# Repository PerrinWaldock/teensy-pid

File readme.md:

# Teensy-based Intensity Feedback Controller Guide

This repository contains code and PCBs for creating Teensy microcontroller-based feedback controllers. They have been used to control the laser intensity on ultracold atom experiments because (a) they are relatively inexpensive and (b) they provide faster rise times than similarly-priced analog feedback controllers.

When used to lock to itself, the latest version of the PCB and firmwarecan achieve 
* a loop rate of 100 kHz
* a standard deviation of TODO
* a rise time of <10 us

## PCB-free Feedback Controller

The code in the `multistate` branch can be used without the PCB. It can only run a Teensy 3.2 because that microcontroller has 5V-tolerant digital inputs, and an inbuilt DAC. It uses two digital signals from digital outputs to select one of four setpoints which are configured over USB. It controls the voltage into a XM-B6H4-0404C-01.

However, this setup has some flaws:
* the inbuilt ADC and DAC are noisy, with only ~8-10 usable bits. This limits the feedback stability shown in the above posts.
* there is no input anti-aliasing filter
* the connections are soldered together on stripboard. The digital input controlling the LSB of the state is currently loose, so the feedback controller occasionally malfunctions when the digital input is not connected to the microcontroller
* the Teensy 3.2 is currently EOL so it is challenging to find a replacement.

A replacement PCB was built that provides the following features:
* input anti-aliasing filtering
* input and output buffering
* input over-voltage protection for both digital and analog inputs
* 16-bit ADCs and DACs
* a faster (600 MHz) microcontroller
* a separate +5V power supply for all analog electronics
* space on the board to mount an XM-B6H4-0404C-01.

The new PCB and its corresponding control code is in the `master` branch of the repository. Below is a guide to the PCB and control code:

## PCB Important Components
The KiCAD design files and schematics are in the schematics folder of this repository. Below is a guide to some components that can be populated or depopulated to change the performance characteristics of the board:
* R1: Populate this to give this board a 50-ohm terminated input. This can be useful when interfacing with a [PDA100A2](https://www.thorlabs.com/thorproduct.cfm?partnumber=PDA100A2) because they produce a 0-5V output when terminated with a 50 ohm load.
  * One can also modify the values of R1, R2 to remove a DC offset from the input signal, or modify the values of R7 and R9 to amplify the input. Useful if the input is a small signal.
* R3: Populate this to bypass the input op amp. Do not do this without first disconnecting the op amp from by depopulating R2 and R9. Often used when R15 and R17 are populated to use the Teensy internal ADC instead of the external ADC (not recommended).
* C1 and R7: Change these values to change the input op amp filter (currently not populated).
* R16 and R18. ONLY POPULATE ONE OF THESE AT A TIME. Used to select 5V or 3.3V reference. If 5V reference is selected (R18), make sure to depopulate R6 so that the input voltage range is the full 0V-5V.
* R34: Populate to use external 5V instead of USB 5V power. DO NOT DO THIS WITHOUT FIRST COVERING THE PIN THAT SUPPLIES POWER ON THE USB CABLE: https://community.octoprint.org/t/put-tape-on-the-5v-pin-why-and-how/13574
* R40: Populate to bypass the output buffer. Do not do this without first disconnecting the op amp by depopulating R41 and FB2.

## Software Important Preprocessor Directives
`pins.h` specifies the IO pins:
* `PIN_REFERENCE0` and `PIN_REFERENCE1` are used to select which preprogrammed set voltage the feedback controller will try to attain.
* `PIN_REFERENCE` can be used as a traditional analog setpoint (NOTE: The PCB is not currently set up to support this)

The `settings.h` file can be changed to modify the feedback controller's behaviour:
* `DEFAULT_KP`, `DEFAULT_KI`, and `DEFAULT_KD` are the default values for the PID constants. They may be overwritten on startup if `LOAD_ON_STARTUP` is enabled.
* `DEFAULT_LOOP_RATE` sets the default loop rate for the feedback controller. It may be overwritten on startup. If `PRECISE_LOOP_TIMING` is true, the feedback controller will run the feedback control loop at the loop rate; otherwise, the loop rate is ignored and the control loop will run as fast as possible. Disabling the precise timing increases the maximum frequency that can be compensated for but means that the units of the PID constants are incorrect.
* `OUTPUT_SETTLE_DELAY_US` should be set to the response time of the output stage (e.g. if controlling an AOM, the response time of the voltage variable attenuator). It is a delay that kicks in immediately after the set point changes from off to on.
  * When the output changes state from off (below the minimum set point) to on (between the minimum and maximum setpoint), the feedback calculation is skipped for the first output, and only the feedforward value is used. This allows the feedback controller to rapidly approach the desired value. However, it takes a finite amount of time for the system to reach the desired value. This delay stops the next feedback measurement from being taken before the system settles to its new state.
* `SERIAL_BAUD` sets the baud rate to communicate with the computer. Comment it out to disable USB communication
  * `SERIAL_CHECK_PERIOD_MS` sets the period to communicate with the host computer. `DEFAULT_PRINT_PERIOD_MS` sets the print period of the PID state.
* `INPUT_MODE` sets the type of input that the feedback controller uses to select its state. `DIGITAL_INPUT` selects preprogrammed set voltage number `PIN_REFERENCE1*2 + PIN_REFERENCE0`, `ANALOG_INPUT` uses the voltage on `PIN_REFERENCE`, and `SOFTWARE_INPUT` only accepts software changes to the set voltage. Note that the `ANALOG_INPUT` mode is not currently well-tested.
  * It may be advantageous to reduce `ANALOG_REFERENCE_RESOLUTION` to 8 or lower to speed up the loop frequency.
  * `NUM_SETPOINTS` is the number of setpoints that can be selected in digital mode. Do not change this without changing the PCB and number of setpoint pins.
* `FEEDFORWARD` enables feedforward control. One can characterize the transfer function of the system via a serial command, then perform corrections to the feedforward function using PID. It generally produces faster rise times than standard PID feedback control, but the `CALIBRATION_SETTLE_DELAY_US` value must be set carefully so that the feedforward array is generated accurately.
* `NEGATIVE_OUTPUT_SLOPE` should be set to true if a larger output voltage should produce a smaller input voltage and vice versa.
* `SAVE_DATA` will give the option to save PID constants, loop frequency, setpoint and output limits, setpoints, and feedforward data.
  * If `LOAD_ON_STARTUP`, then these constants will be loaded on startup, overriding the default values.
* `DEFAULT_SETPOINT` is the default setpoint voltage. This will be overridden if `LOAD_ON_STARTUP` is set to true.
* `DEFAULT_READ_AVERAGES_POWER` sets the default number of averages that will be taken before using a feedback measurement. The number of averages is two to the power of the value. This will be overridden if `LOAD_ON_STARTUP` is set to true.
  * If in analog mode, `ANALOG_READ_AVERAGES` is the number of averages for the setpoint value reading, and `ANALOG_REFERENCE_RESOLUTION` sets the number of bits for the measurement.
* if `RECORD_FEEDBACK_ALL_ITERATIONS` is true, then the feedback voltage will always be measured, even if it isn't used (such as immediately after a setpoint is changed). This can be helpful for debugging but should be turned off for performance.
* if `TIME_FEEDBACK_LOOP`, the length of time to perform the pid calculation will be timed.
* if `RECORD_INPUT`, input values will be logged to RAM. Helpful for debugging.
* `CALIBRATION_AVERAGES` sets the number of measurements to take of each point when generating the feedforward lookup array
  * `CALIBRATION_PRE_SETTLE_DELAY_US` sets how long to wait (in us) for the system to settle before measuring points for the feedforward lookup array
  * `CALIBRATION_SETTLE_DELAY_US` sets how how long to wait (in us) for the system to settle between points while measuring points for the feedforward lookup array

## Serial Commands
Connect the feedback controller using Putty or the Arduino IDE to tune the feedback parameters, adjust the setpoint, loop frequency, and other parameters.

Note that the FeedbackController class in the Prometheus repository uses some of the following serial commands in order to set the laser power to a certain level at specific points in a recipe.

Commands:
* `h` to print the help menu
* `kp=x` to set the proportional constant. `kp?` to print the proportional constant. Similar for `ki` and `kd`.
* `sv0=0.5` to set the 0th preprogammed set voltage to 0.5 volts. similar for `sv1`, `sv2`, and `sv3`. use `sv?` to view all for set voltages. Use `sp` to set the value as an integer instead of as a voltage.
* `ls=0.05` to set the minimum setpoint to 0.05V. Set to some value close to the minimum attainable feedback value. Used to prevent integral wind-up if the system cannot reach the set value.
* `ls=4.5` to set the maximum setpoint to 4.5V. Set to some value close to the maximum attainable feedback value. Used to prevent integral wind-up if the system cannot reach the set value.
* `lf=2000` to set the loop frequency to 2000 Hz. lf? to view the loop frequency. Make sure that the loop period is not less than the time the controller takes to perform a pid calculation.
* `ra=2` to set the number of read averages to four. The formula is <read averages>=2^x where x is an integer -- this ensures that the number of read averages is always a multiple of two, which speeds up the averaging process. Use ra? to view the number of read averages
* `pa=1` to enable feedback control, `pa=0` to disable it
* `po=1` to print sample feedback control values. `po=0` to disable the printed sample feedback control values. A sample string would be `s:6553	 f:6553	 ff:13490	 o:12850	 t:16`, where s refers to the set voltage, f is the feedback voltage, ff is the output voltage the feedforward term recommends, o is the output voltage of the controller, and t is the time the controller took to perform the feedback calculation. All voltages are written as integers, and the time is in microseconds. Write `po=2` to display the values as voltages instead.
* `cf` to create the feedforward function. This will also set the setpoint limits to slightly inside the feedback controller range. Write `cd?` to print out the calibration data, and `ce?` to print out the calibration extrema (minimum and maximum set voltage).
* `ew=w` to write the feedback constants, loop rate, and calibration data to EEPROM so they are persistent after startup. `ew=r` to read all data from EEPROM. Useful when tuning to restore the feedback controller to a working state.
* `cl` to clear the integral term and reset the controller state -- helpful if the integral term has spooled up.

Typical usage:
Via the USB serial connection, enter the following comnmands:
* `cf=1` (to calibrate the feedforward function)
* `ce?` (to print the minimum and maximum values that can theoretically be set)
* `sv0=1` (to set the set voltage to 1V. Replace the 1 with a value close to the maximum set voltage found above)
* `po=2` (monitor the output, ensure that it is stable)
* `po=0` (turn off the output)
* set the tuning parameters and loop frequency with `ki=x`,`kp=x`,`kd=0`, `lf=100000`. Ensure that the calculation time does not exceed the loop period. Adjust parameters until performance is satisfactory.

### Notes for the UBC QDG Lab
To achieve a rapid response time, the set point needs to be selected using the digital inputs. It is easiest to do so by programming the desired setpoints ahead of time, then selecting the desired set point via the digital input. Code to do this is in the FeedbackController class in hardware/FeedbackController in the [Prometheus repository](https://qdg-code.phas.ubc.ca:2633/Perrin/PrometheusPython). This class automatically uses USB commands to assign different set voltages to different set voltage states during the recipe's compile time, then uses digital outputs to select those states while the recipe is executing. It automatically calibrates the feedforward function during compile time.

## Programming Instructions
This was developed as a PlatformIO project in VS Code. The easiest way to modify and compile it is to get the PlatformIO VS Code extension

## GUI and Python Scripts

## Future Work To Do
### Speeding things up
Currently, the microcontroller is set to use a 600 MHz clock. Attaching a heatsink to the processor should allow high clock rates.

Higher clock rates may disrupt communication with the ADC and DAC. To improve the ADC and DAC throughput:
* connect an oscilloscope to the data lines as well as the analog output
* change "#define dacdigwr(p, s) digitalWrite(p, s)" in dac.ino to "#define dacdigwr(p, s) digitalWriteFast(p, s)"
* adjust WRITE_DELAY_NS such that the DAC still consistantly writes the correct value
* similarly, adjust WAIT_TIME_NS and CLOCK_DELAY_NS in adc.ino.
* R21, R22, R23, R24, R25, R26, R30, R31, and R32 may need to be adjusted to a smaller value to accommodate higher clock rates. Choose values that are as large as possible while still allowing the clock to remain high for the specified time in the ADC and DAC datasheets.

### Testing
* The latest version of the PCB (V3.0) has not been tested as a feedback controller for a laser intensity lock.
* Using the analog input as a setpoint also is not well-tested, and may contain bugs.

### New Algorithms
This controller should be usable for a gradient-descent saturated adsorption lock algorithm.

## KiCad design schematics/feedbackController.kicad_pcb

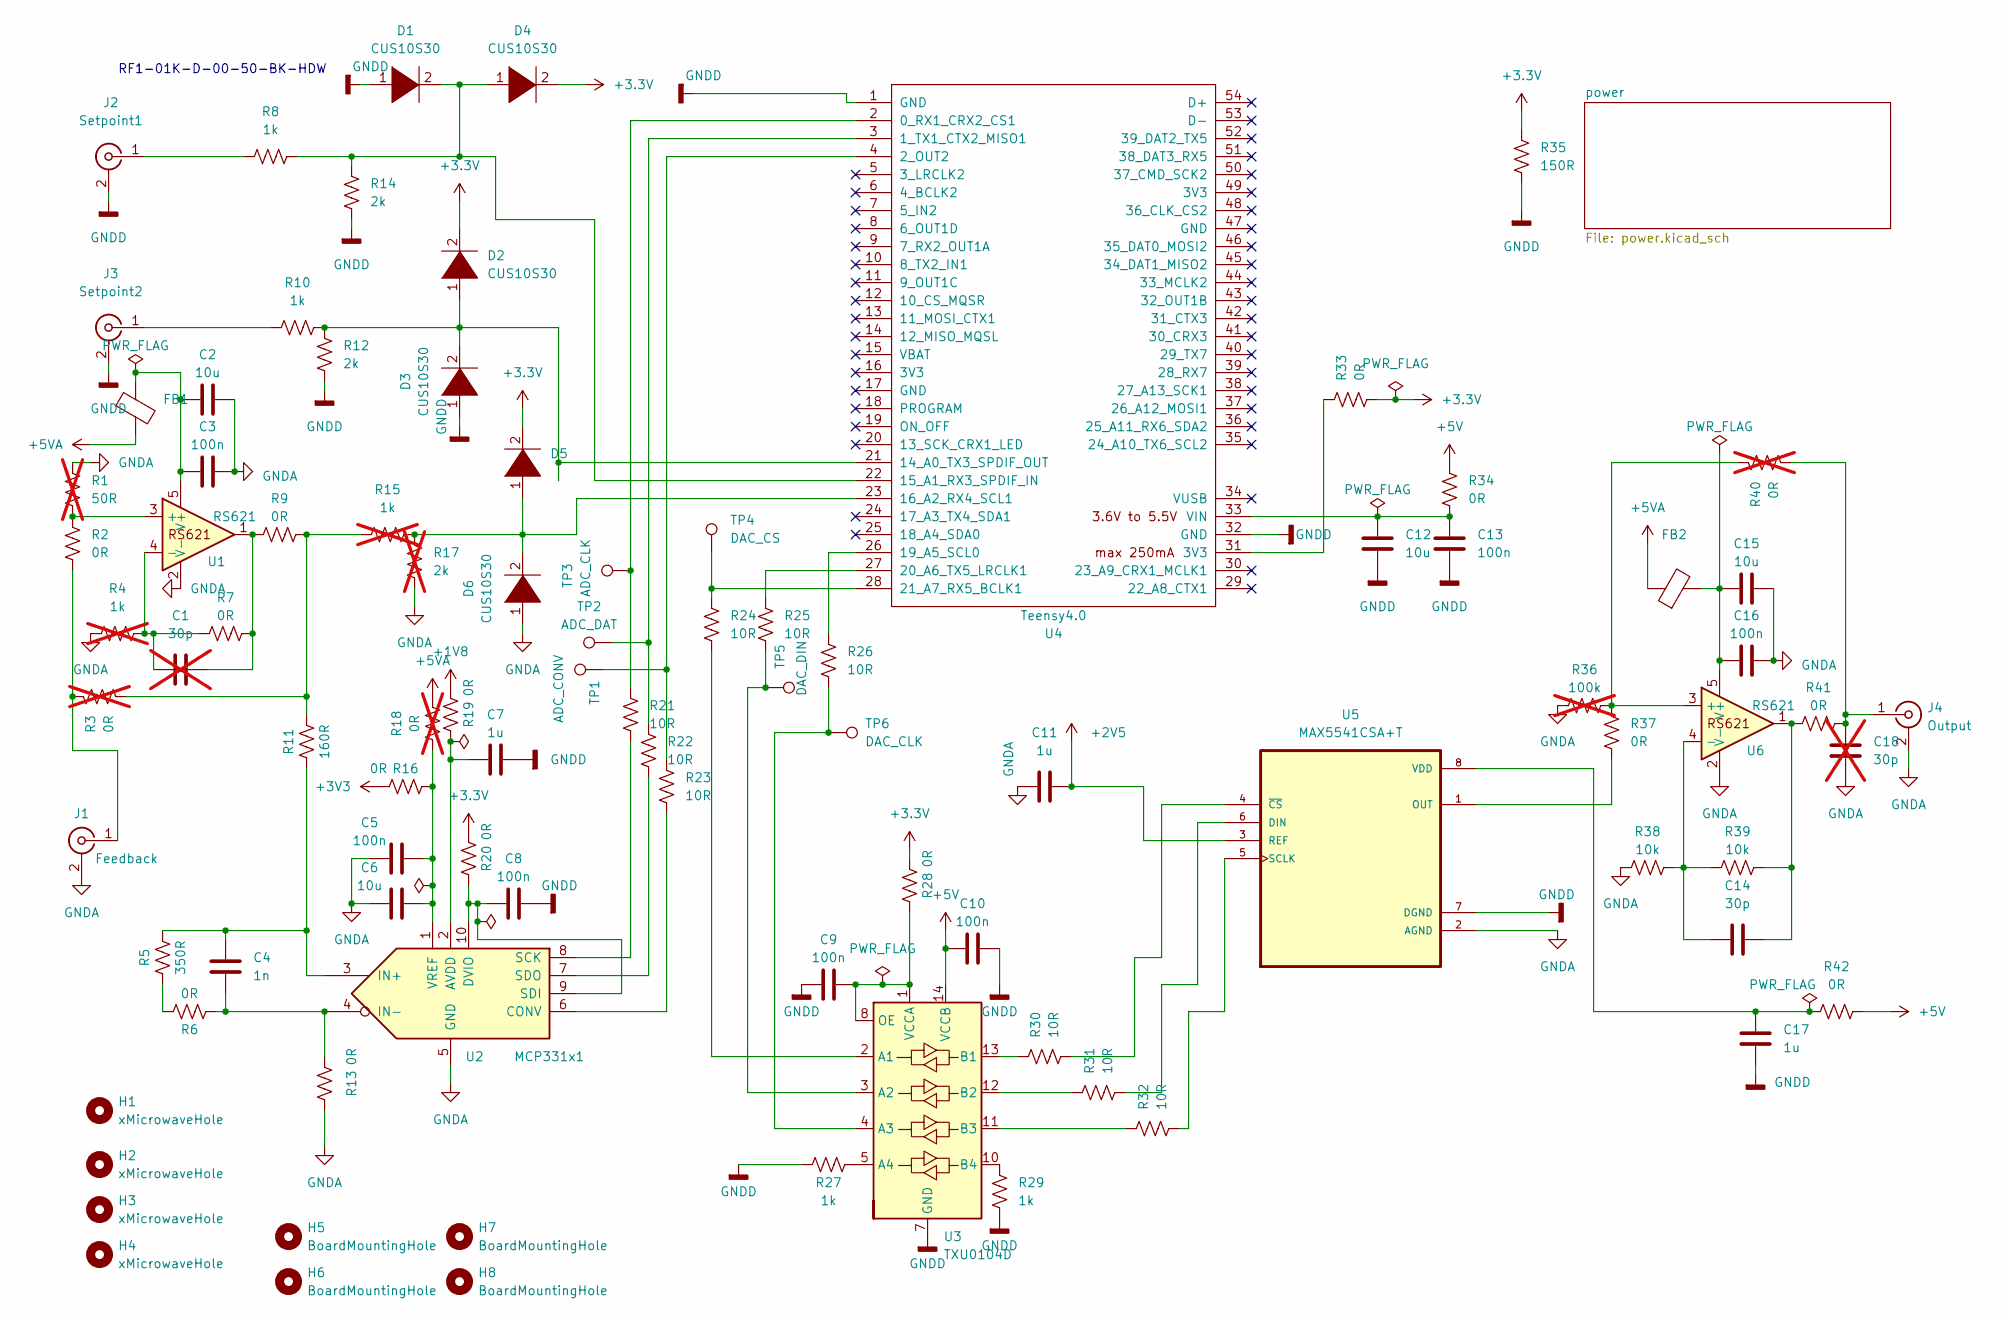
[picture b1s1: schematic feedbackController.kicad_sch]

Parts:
C1, C18: 30p; C_0805_2012Metric; not fitted
C2, C6, C12, C15: 10u; C_0805_2012Metric
C3, C5, C8, C9, C10, C13, C16: 100n; C_0805_2012Metric
C4: 1n; C_0805_2012Metric
C7, C11, C17: 1u; C_0805_2012Metric
C14: 30p; C_0805_2012Metric
D1, D2, D3, D4, D5, D6: CUS10S30; D_SOD-323_HandSoldering
FB1, FB2: FerriteBead; R_0805_2012Metric_Pad1.20x1.40mm_HandSolder
H1, H2, H3, H4: xMicrowaveHole; MountingHole_2.1mm
H5, H6, H7, H8: BoardMountingHole; MountingHole_3.2mm_M3
J1: Feedback; BNC_Amphenol_B6252HB-NPP3G-50_Horizontal
J2: Setpoint1; BNC_Amphenol_B6252HB-NPP3G-50_Horizontal
J3: Setpoint2; BNC_Amphenol_B6252HB-NPP3G-50_Horizontal
J4: Output; BNC_Amphenol_B6252HB-NPP3G-50_Horizontal
R1: 50R; R_0805_2012Metric; not fitted
R2, R6, R7, R9, R13, R16, R19, R20, R28, R33, R34, R37, R41, R42: 0R; R_0805_2012Metric
R3, R18, R40: 0R; R_0805_2012Metric; not fitted
R4, R15: 1k; R_0805_2012Metric; not fitted
R5: 350R; R_0805_2012Metric
R8, R10, R27, R29: 1k; R_0805_2012Metric
R11: 160R; R_0805_2012Metric
R12, R14: 2k; R_0805_2012Metric
R17: 2k; R_0805_2012Metric; not fitted
R21, R22, R23, R24, R25, R26, R30, R31, R32: 10R; R_0805_2012Metric
R35: 150R; R_0805_2012Metric
R36: 100k; R_0805_2012Metric; not fitted
R38, R39: 10k; R_0805_2012Metric
TP1: ADC_CONV; TestPoint_Loop_D2.50mm_Drill1.0mm
TP2: ADC_DAT; TestPoint_Loop_D2.50mm_Drill1.0mm
TP3: ADC_CLK; TestPoint_Loop_D2.50mm_Drill1.0mm
TP4: DAC_CS; TestPoint_Loop_D2.50mm_Drill1.0mm
TP5: DAC_DIN; TestPoint_Loop_D2.50mm_Drill1.0mm
TP6: DAC_CLK; TestPoint_Loop_D2.50mm_Drill1.0mm
U1, U6: RS621; SOT-23-5_HandSoldering
U2: MCP331x1; MSOP-10_3x3mm_P0.5mm
U3: TXU0104D; SOIC-14_3.9x8.7mm_P1.27mm
U4: Teensy4.0; Teensy40
U5: MAX5541CSA+T; SOIC-8_3.9x4.9mm_P1.27mm

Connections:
+1V8: R19.2; also elsewhere on the board
+2V5: C11.2, U5.3 (REF); also elsewhere on the board
+3.3V: D2.2 (A), D4.2 (A), D5.2 (A), R20.2, R28.2, R33.1, R35.1; also elsewhere on the board
+3V3: R16.2; also elsewhere on the board
+5V: C10.1, R34.2, R42.2, U3.14 (VCCB); also elsewhere on the board
+5VA: FB1.2, FB2.1, R18.2; also elsewhere on the board
GNDA: C2.2, C3.2, C5.1, C6.1, C11.1, C15.2, C16.2, C18.2, D6.1 (K), J1.2 (Ext), J4.2 (Ext), R1.1, R4.1, R13.1, R17.2, R36.1, R38.1, U1.2 (V-), U2.5 (GND), U5.2 (AGND), U6.2 (V-); also elsewhere on the board
GNDD: C7.2, C8.2, C9.1, C10.2, C12.2, C13.2, C17.2, D1.1 (K), D3.1 (K), J2.2 (Ext), J3.2 (Ext), R12.2, R14.2, R27.1, R29.2, R35.2, U3.7 (GND), U4.1 (GND), U4.32 (GND), U5.7 (DGND); also elsewhere on the board
unnamed: C1.2, R7.2, R9.1, U1.1
unnamed: C14.2, R39.2, R41.1, U6.1
unnamed: D1.2 (A), D4.1 (K), R8.2, R14.1, U4.22 (15_A1_RX3_SPDIF_IN)
unnamed: D2.1 (K), D3.2 (A), R10.2, R12.1, U4.21 (14_A0_TX3_SPDIF_OUT)
unnamed: D5.1 (K), D6.2 (A), R15.2, R17.1, U4.23 (16_A2_RX4_SCL1)
unnamed: J1.1 (In), R2.2, R3.1
unnamed: J2.1 (In), R8.1
unnamed: J3.1 (In), R10.1
unnamed: C18.1, J4.1 (In), R40.2, R41.2
unnamed: R5.1, R6.2
unnamed: R3.2, R9.2, R11.2, R15.1
unnamed: R33.2, U4.31 (3V3)
unnamed: R1.2, R2.1, U1.3 (+)
unnamed: C1.1, R4.2, R7.1, U1.4 (-)
unnamed: C2.1, C3.1, FB1.1, U1.5 (V+)
unnamed: C7.1, R19.1, U2.2 (AVDD)
unnamed: R23.1, U2.6 (CONV)
unnamed: C8.1, R20.1, U2.9 (SDI), U2.10 (DVIO)
unnamed: C4.1, R5.2, R11.1, U2.3 (IN+)
unnamed: C4.2, R6.1, R13.2, U2.4 (IN-)
unnamed: R21.1, U2.8 (SCK)
unnamed: R22.1, U2.7 (SDO)
unnamed: C5.2, C6.2, R16.1, R18.1, U2.1 (VREF)
unnamed: R24.1, U3.2 (A1)
unnamed: R25.1, TP5.1, U3.3 (A2)
unnamed: R26.1, TP6.1, U3.4 (A3)
unnamed: R27.2, U3.5 (A4)
unnamed: R30.2, U3.13 (B1)
unnamed: R31.2, U3.12 (B2)
unnamed: R32.2, U3.11 (B3)
unnamed: R29.1, U3.10 (B4)
unnamed: C9.2, R28.1, U3.1 (VCCA), U3.8 (OE)
unnamed: R21.2, TP3.1, U4.2 (0_RX1_CRX2_CS1)
unnamed: R22.2, TP2.1, U4.3 (1_TX1_CTX2_MISO1)
unnamed: R23.2, TP1.1, U4.4 (2_OUT2)
unnamed: R26.2, U4.26 (19_A5_SCL0)
unnamed: R25.2, U4.27 (20_A6_TX5_LRCLK1)
unnamed: R24.2, TP4.1, U4.28 (21_A7_RX5_BCLK1)
unnamed: C12.1, C13.1, R34.1, U4.33 (VIN)
unnamed: R31.1, U5.6 (DIN)
unnamed: R37.1, U5.1 (OUT)
unnamed: R32.1, U5.5 (SCLK)
unnamed: C17.1, R42.1, U5.8 (VDD)
unnamed: R30.1, U5.4 (~CS)
unnamed: R36.2, R37.2, R40.1, U6.3 (+)
unnamed: C14.1, R38.2, R39.1, U6.4 (-)
unnamed: C15.1, C16.1, FB2.2, U6.5 (V+)

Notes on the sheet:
RF1-01K-D-00-50-BK-HDW

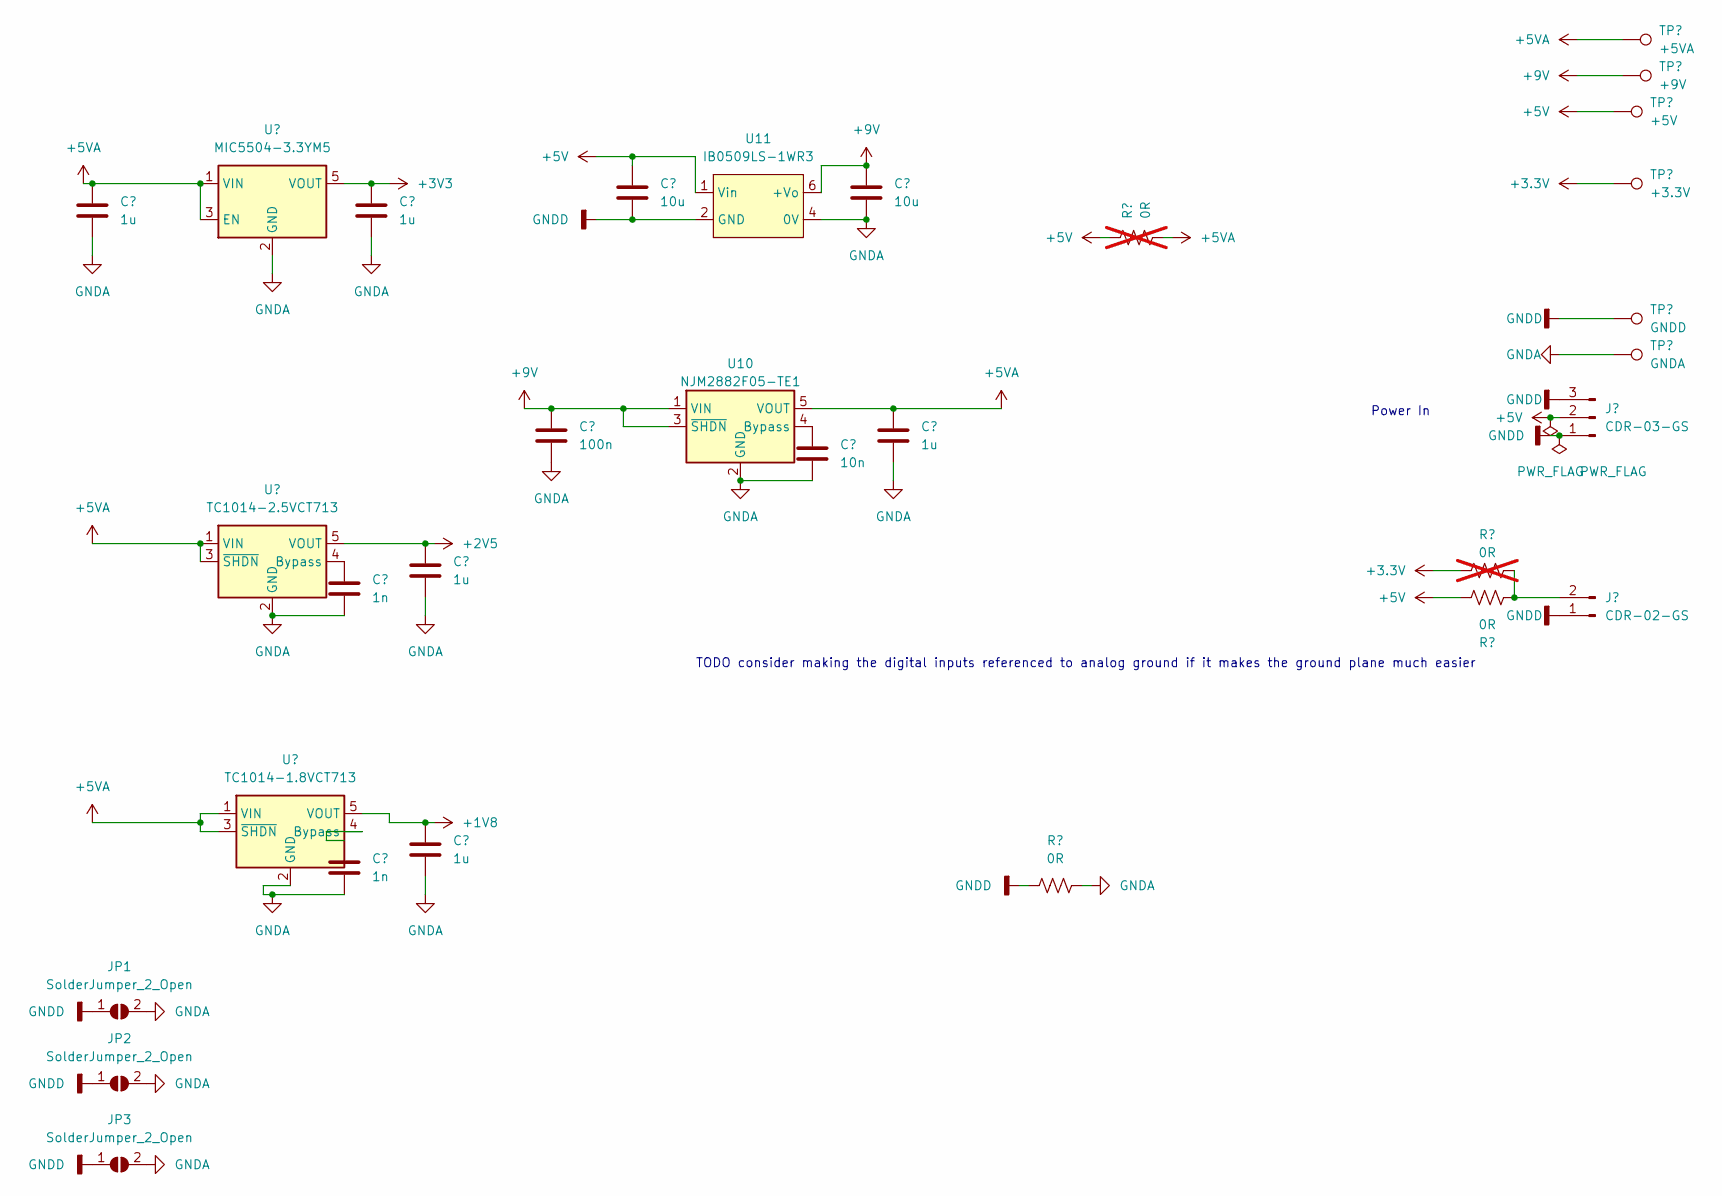
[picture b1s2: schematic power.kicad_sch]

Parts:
C19, C22, C23, C24, C29: 1u; C_0805_2012Metric
C20, C21: 1n; C_0805_2012Metric
C25: 100n; C_0805_2012Metric
C26, C28: 10u; C_0805_2012Metric
C27: 10n; C_0805_2012Metric
J5: CDR-03-GS; PinSocket_1x03_P2.54mm_Vertical
J6: CDR-02-GS; PinHeader_1x02_P2.54mm_Vertical
JP1, JP2, JP3: SolderJumper_2_Open; SolderJumper-2_P1.3mm_Open_Pad1.0x1.5mm
R43, R46: 0R; R_0805_2012Metric
R44, R45: 0R; R_0805_2012Metric; not fitted
TP7: +5V; TestPoint_Loop_D2.50mm_Drill1.0mm
TP8: +3.3V; TestPoint_Loop_D2.50mm_Drill1.0mm
TP9: GNDD; TestPoint_Loop_D2.50mm_Drill1.0mm
TP10: GNDA; TestPoint_Loop_D2.50mm_Drill1.0mm
TP11: +5VA; TestPoint_Loop_D2.50mm_Drill1.0mm
TP12: +9V; TestPoint_Loop_D2.50mm_Drill1.0mm
U7: MIC5504-3.3YM5; SOT-23-5
U8: TC1014-2.5VCT713; SOT-23-5
U9: TC1014-1.8VCT713; SOT-23-5
U10: NJM2882F05-TE1; SOT-23-5_HandSoldering
U11: IB0509LS-1WR3; IB05_LS-1WR3

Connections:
+1V8: C24.1, U9.5 (VOUT); also elsewhere on the board
+2V5: C23.1, U8.5 (VOUT); also elsewhere on the board
+3.3V: R45.2, TP8.1; also elsewhere on the board
+3V3: C22.1, U7.5 (VOUT); also elsewhere on the board
+5V: C26.1, J5.2, R44.2, R46.2, TP7.1, U11.1 (Vin); also elsewhere on the board
+5VA: C19.1, C29.1, R44.1, TP11.1, U7.1 (VIN), U7.3 (EN), U8.1 (VIN), U8.3 (~SHDN), U9.1 (VIN), U9.3 (~SHDN), U10.5 (VOUT); also elsewhere on the board
+9V: C25.1, C28.1, TP12.1, U10.1 (VIN), U10.3 (~SHDN), U11.6 (+Vo)
GNDA: C19.2, C20.2, C21.2, C22.2, C23.2, C24.2, C25.2, C27.2, C28.2, C29.2, JP1.2 (B), JP2.2 (B), JP3.2 (B), R43.2, TP10.1, U7.2 (GND), U8.2 (GND), U9.2 (GND), U10.2 (GND), U11.4 (0V); also elsewhere on the board
GNDD: C26.2, J5.1, J5.3, J6.1, JP1.1 (A), JP2.1 (A), JP3.1 (A), R43.1, TP9.1, U11.2 (GND); also elsewhere on the board
unnamed: J6.2, R45.1, R46.1
unnamed: C20.1, U8.4 (Bypass)
unnamed: C21.1, U9.4 (Bypass)
unnamed: C27.1, U10.4 (Bypass)

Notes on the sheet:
TODO consider making the digital inputs referenced to analog ground if it makes the ground plane much easier
Power In

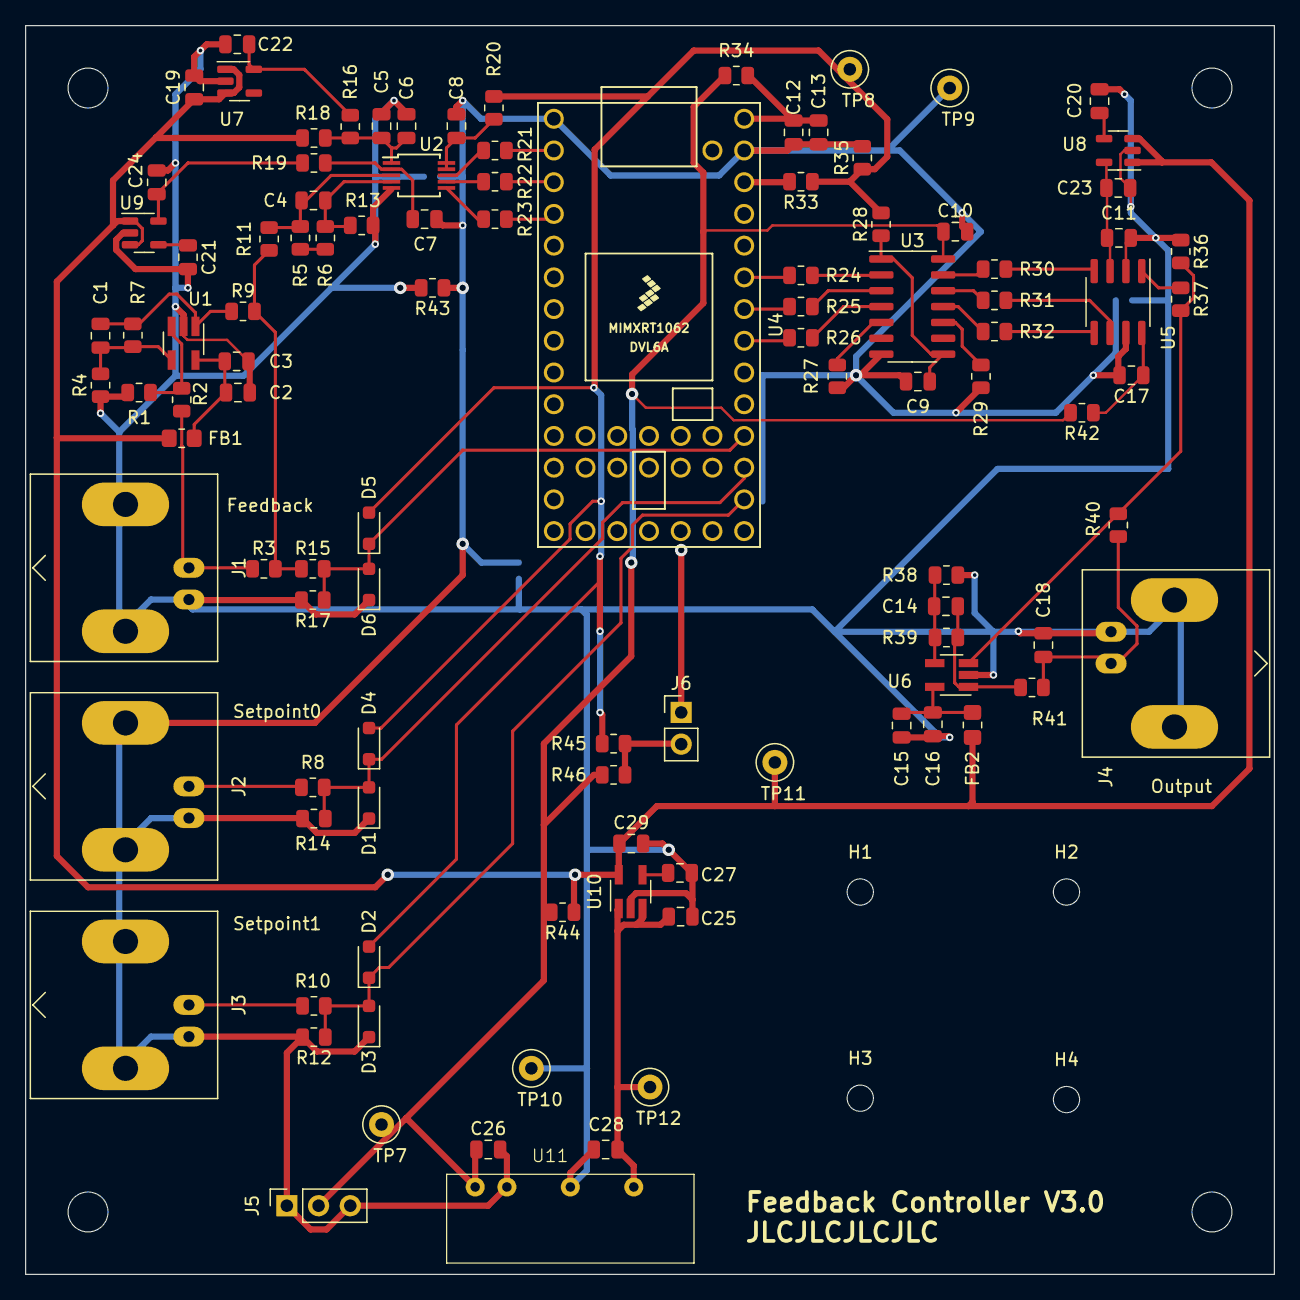
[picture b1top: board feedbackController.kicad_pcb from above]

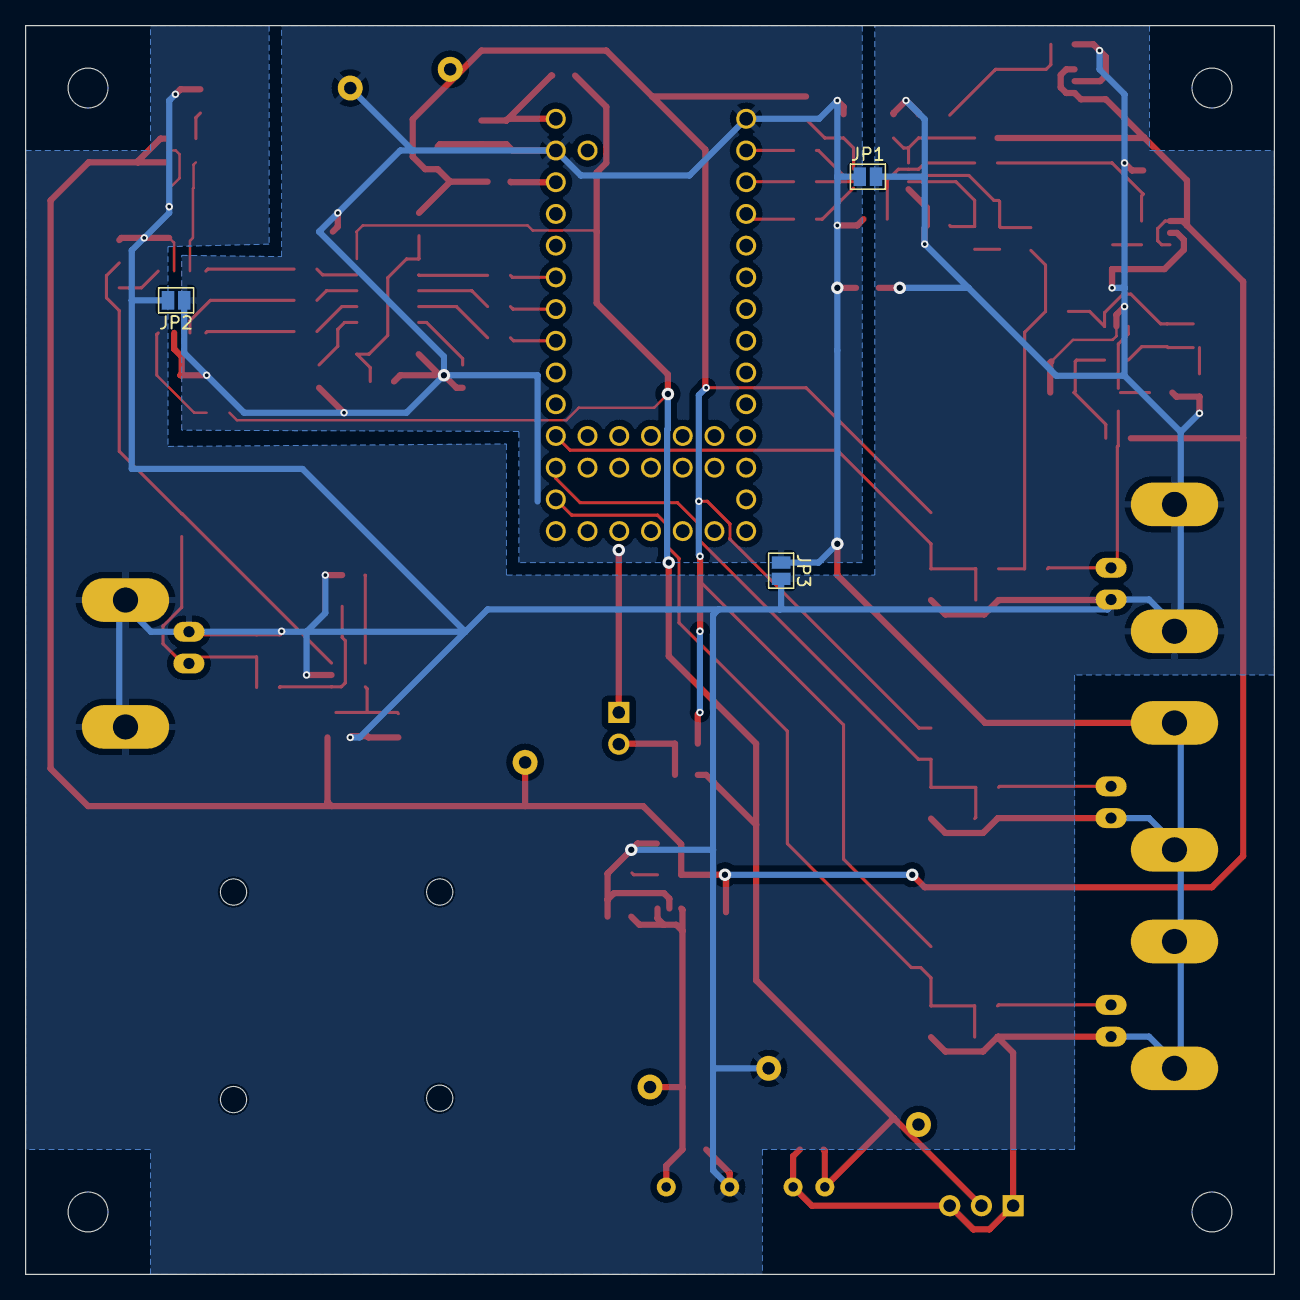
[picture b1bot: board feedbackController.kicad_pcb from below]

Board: 2 copper layers, 100.0 x 100.0 mm, 117 parts (3 on the bottom side), 60 nets.

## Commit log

2020-09-19 adding serial control
2020-09-19 added setpoint serial control
2020-09-25 changing to be used with teensy 3.2
2020-09-25 added code to set voltage
2020-10-06 committing changes
2020-10-06 上传文件至 ''
2020-10-14 added digital and analog control
2020-10-14 removing PID.ino
2020-10-14 fixed ki
2020-10-14 Adding helpful advice
2020-10-14 set default to high input via pullup resistor
2020-10-14 fixing analog control code and turning off serial code
2020-10-15 added untested output limiting code
2020-10-20 broken into header and file
2021-09-04 increased minimum threshold to prevent integral wind-up after turning off
2021-09-08 possible feedforward code added
2022-02-17 added code for the Teensy 3.2
2022-02-17 fixed typos
2022-09-28 fixed feedforward digital control
2022-09-28 added code that prints the input extrema and increases read averages for calibration data
2022-09-30 fixed negative feedforward control lookup generation
2022-10-01 added protype code to save parameters to eeprom
2022-10-01 fixed bugs in the eeprom write/read code, disabled limits reading because there's no way of over-writing it, fixed sign issues with PID output
2022-10-01 increased response speed for digital inputs
2022-10-03 fixed typo that was disabling feedforward control
2022-10-18 added ability to change loop rate
2022-12-08 adding any changes
2022-12-11 fixing indentation
2023-01-27 committing current changes to feedback controller before adding multi-state inputs
2023-08-29 refactoring repository and adding schematics
2023-09-14 added prototype control code
2023-09-14 minor fixes to feedback control code
2023-09-15 added voltage to print output
2023-09-19 adding schematic changes for v2.1
2023-09-20 adding logging code for debugging step response
2023-09-20 fixed bug that causes overshoot when changing level via USB
2023-09-20 fixing help function
2023-09-30 commit before branch
2023-10-25 bug fixes and adding separate pins header file
2023-11-05 adding readme
2023-11-05 updating README
2023-11-05 Update 'readme.md'
2024-10-26 moving order to cart
2024-10-26 attempting to remove submodule
2024-10-26 removing git subdirectories
2024-11-09 adding proposed changes
2024-11-17 temporary partial refactor
2024-11-25 got refactored code to compile
2024-11-26 added a setpoint manager
2024-11-27 fixed build errors
2024-11-30 fixed data logger logic
2024-12-03 fixed initialization order
2024-12-03 removed unneeded code
2024-12-08 refactored to pass same object to all handlers
2024-12-08 use same object for all handlers
2024-12-08 changed to using handlers with the correct argument type
2024-12-09 switched to using pointers as command parser objects
2024-12-10 fixed misc bigs in feedback controller
2024-12-11 added options to save feedback even when calc skipped
2025-01-06 fixed bugs in control code
2025-01-06 fixed pid logic
2025-01-09 fixed bugs in eeprom code
2025-01-09 starting with pid active
2025-01-13 enabled data logging
2025-01-13 added settings guide to readme file
2025-01-13 added clarifying comments
2025-01-14 fixed logging for more than 1000 bytes
2025-01-19 added basic test code
2025-01-19 fixed feedback controller code
2025-01-19 added step response and stability test code
2025-01-19 added slew-rate dependant delay
2025-01-19 cache last output value
2025-01-19 refined tests
2025-01-19 added timestamps to logs
2025-01-20 added loose scores to analysis code
2025-01-20 printing more information when testing performance
2025-01-26 fixed bug in delay code
2025-01-26 tweaked rise time behaviour
2025-01-26 added method to find parameters for optimal stability
2025-01-26 added command to display limits
2025-02-01 created hello world gui
2025-02-01 switched to different way of launching application
2025-02-06 minor bug fixes
2025-03-16 added further explanation
2025-07-01 added virtual controller
2025-10-03 add simulation code
2025-10-07 add more simulating infrastructure
2025-10-08 fix pid tuning algorithm
2025-10-13 tweaked fpid model to include max ramp rate
2025-10-15 remove cached files
2025-10-15 add gitignore
